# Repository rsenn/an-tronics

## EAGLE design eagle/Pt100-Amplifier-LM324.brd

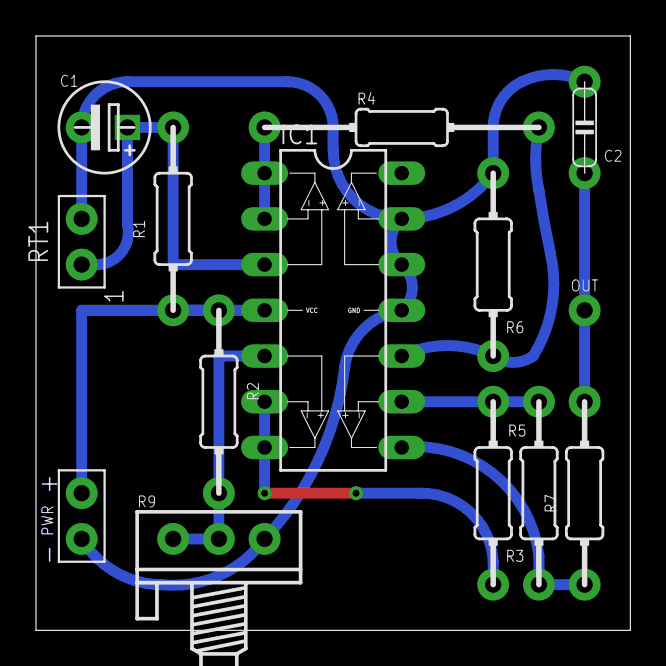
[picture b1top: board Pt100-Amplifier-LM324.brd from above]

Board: 2 copper layers, 33.0 x 33.0 mm, 14 parts (0 on the bottom side), 10 nets.

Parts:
C1: 100uF; E2,5-5
C2: 100nF; C050-020X044/V
IC1: LM324-LM324; DIL14-LM324
OUT: HPORT; SPAD
R1: 1k; 0204/10
R2: 47k; 0204/10
R3: 10k; 0204/10-V
R4: 10k; 0204/15
R5, R6: 47k; 0204/10-V
R7: 220k; 0204/10
R9: POT
RT1: SPAD-2
S5: VCC_GNDPWR-L; PWR-L

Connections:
GND: C1.-, C2.2, IC1.11, IC1.12, IC1.13, R6.2, R9.E, RT1.2, S5.1
unnamed: C1.+, IC1.3, R1.2, RT1.1
unnamed: IC1.1, IC1.2, R4.1
unnamed: IC1.10, R4.2, R6.1
unnamed: IC1.9, R3.2, R5.1
unnamed: IC1.8, R5.2, R7.1
unnamed: C2.1, OUT.1, R7.2
unnamed: IC1.6, IC1.7, R3.1
unnamed: IC1.5, R2.2, R9.A, R9.S
VCC: IC1.4, R1.1, R2.1, S5.2

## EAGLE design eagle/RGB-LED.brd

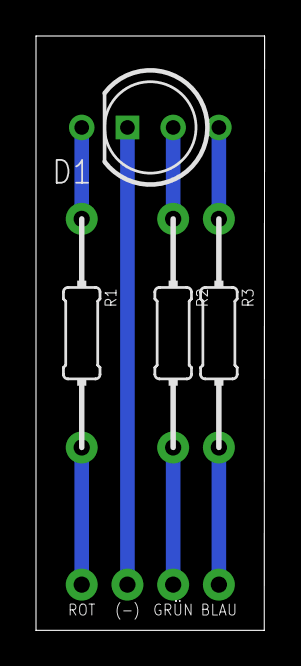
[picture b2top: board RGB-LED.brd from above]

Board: 2 copper layers, 12.7 x 33.0 mm, 8 parts (0 on the bottom side), 7 nets.

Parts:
(-): HPORT; SPAD
BLAU: HPORT; SPAD
D1: RGB-LED-5MM; LED5MM
GRÜN: HPORT; SPAD
R1: 75Ω; 0204/12-V
R2: 39Ω; 0204/12-V
R3: 27Ω; 0204/12-V
ROT: HPORT; SPAD

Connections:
unnamed: D1.1, R1.2
unnamed: D1.3, R2.2
unnamed: D1.4, R3.2
unnamed: R1.1, ROT.1
unnamed: GRÜN.1, R2.1
unnamed: BLAU.1, R3.1
unnamed: (-).1, D1.2

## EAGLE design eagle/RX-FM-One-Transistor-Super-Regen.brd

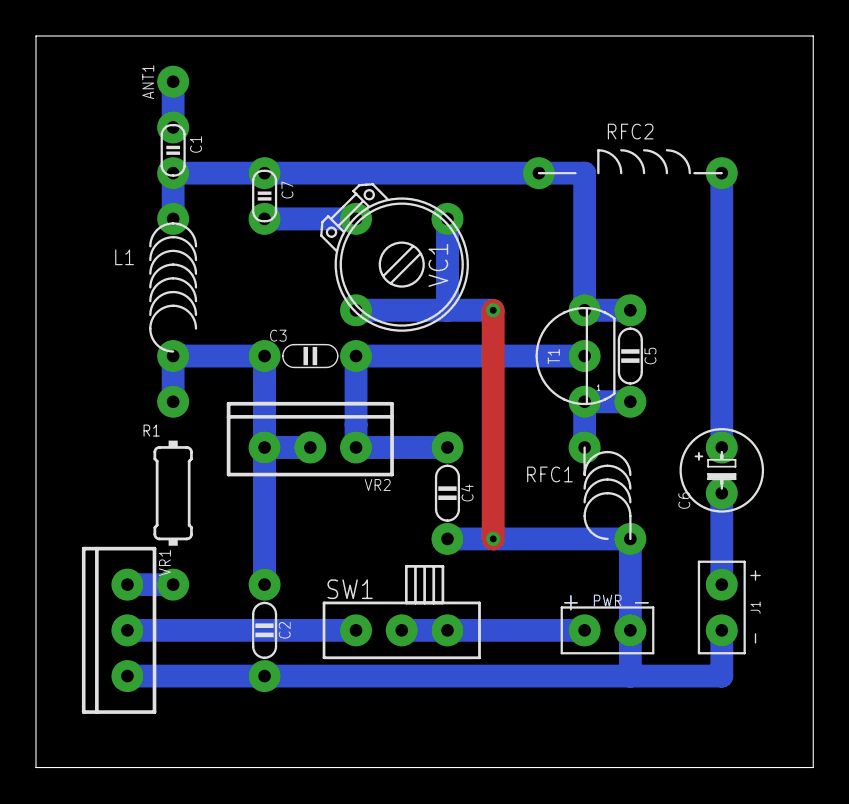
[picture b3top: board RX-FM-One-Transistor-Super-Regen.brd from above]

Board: 2 copper layers, 43.2 x 40.6 mm, 19 parts (0 on the bottom side), 12 nets.

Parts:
ANT1: ANT; SPAD
C1: 5pF; C025-015X024
C2: 0.001; C050-020X036/V
C3: 0.001; C050-020X036
C4: 100pF; C050-020X036/V
C5: 10pF; C050-020X036/V
C6: 10µF; E2,5-4
C7: 47pF; C025-015X024
J1: SPAD+-+-; SPAD+-
L1: 4t; L-04/7-V
R1: 2.2kΩ; 0204/10-V
RFC1: 10µH; L-04-2/5V
RFC2: 10µH; L-03/10
S6: VCC_GNDPWR-R; PWR-R
SW1: SW-SPST-SL-1P2T-H; SLSW-1P2T-H
T1: 2N3904; TO92
VC1: 20pF; TRIM-2222-808
VR1: 10kΩ; TRIM-POT
VR2: 100kΩ; TRIM-POT

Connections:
GND: C2.2, C4.2, J1.1, RFC1.1, S6.1, VC1.1, VC1.3, VR1.E
unnamed: ANT1.1, C1.1
unnamed: C1.2, C5.1, C7.1, L1.1, RFC2.2, T1.3
unnamed: C2.1, C3.1, L1.2, R1.1, VR2.E, VR2.S
unnamed: C7.2, VC1.2
unnamed: R1.2, VR1.A
unnamed: C5.2, RFC1.2, T1.1
unnamed: C3.2, C4.1, T1.2, VR2.A
unnamed: SW1.S, VR1.S
unnamed: C6.+, RFC2.1
unnamed: C6.-, J1.2
VCC: S6.2, SW1.P

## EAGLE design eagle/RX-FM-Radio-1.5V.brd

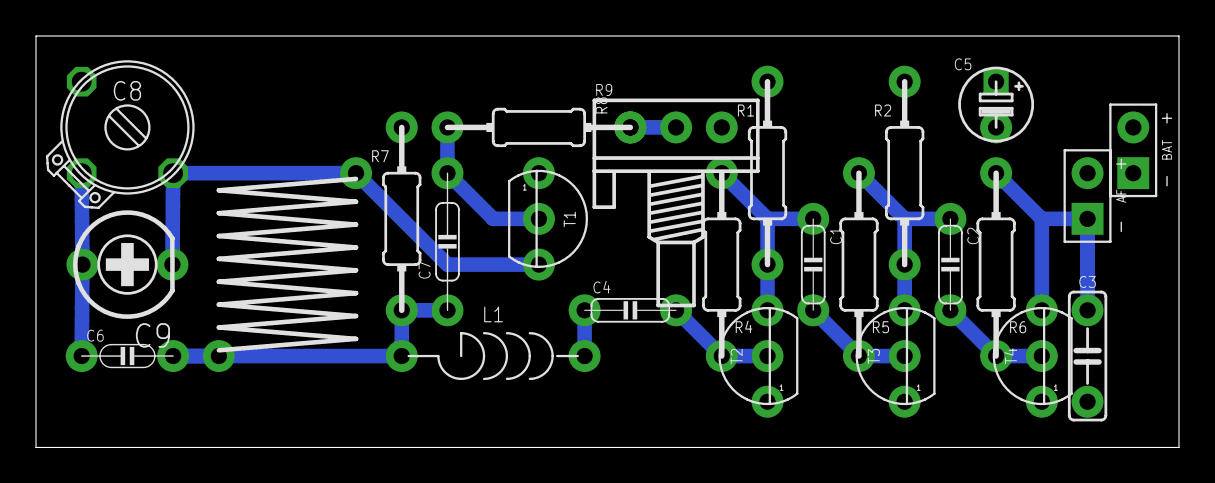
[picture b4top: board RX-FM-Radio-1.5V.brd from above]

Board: 2 copper layers, 63.5 x 22.9 mm, 25 parts (0 on the bottom side), 14 nets.

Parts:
AF: SPAD+-+-; SPAD+-
BAT: SPAD+-+-; SPAD+-
C1: 33nF; C050-020X044
C2: 100nF; C050-020X044
C3: 10nF; C050-025X060
C4: 10nF; C050-020X044
C5: 100μF; E2.5-4/V
C6: 22pF; C050-020X036
C7: 100nF; C075-020X044
C8: 20pF; TRIM-2222-808
C9: 5pF; CTRIMTZ03
L1: 2.2μH; L-03/10
L2: 0.2μH; L-10/10Y
R1, R2: 4.7kΩ; 0204/10-V
R4, R5: 1MΩ; 0204/10-V
R6: 56kΩ; 0204/10-V
R7: 10kΩ; 0204/10-V
R8: 470kΩ; 0204/10-V
R9: 10kΩ; POT
T1, T2, T3, T4: 2N2222; TO92

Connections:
BASE: C7.2, R8.2, T1.2
BIAS: R8.1, R9.S
CAP: C6.1, C8.2, C9.1
COIL: C6.2, C7.1, L1.2, L2.P$2, R7.2
COLL: C8.3, C9.2, L2.P$1, T1.3
GND: BAT.1, C3.2, C5.-, R9.E, T1.1, T2.1, T3.1, T4.1
unnamed: C1.2, R5.1, T3.2
unnamed: C2.1, R2.2, R5.2, T3.3
unnamed: C1.1, R1.2, R4.2, T2.3
unnamed: C2.2, R6.1, T4.2
unnamed: AF.1, C3.1, R6.2, T4.3
unnamed: C4.2, R4.1, T2.2
unnamed: C4.1, L1.1
VCC: AF.2, BAT.2, C5.+, R1.1, R2.1, R7.1, R9.A

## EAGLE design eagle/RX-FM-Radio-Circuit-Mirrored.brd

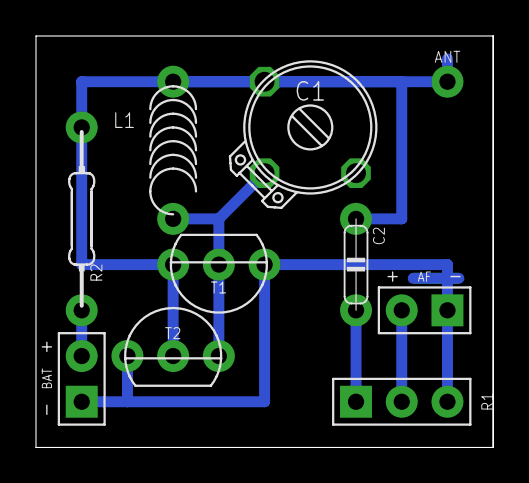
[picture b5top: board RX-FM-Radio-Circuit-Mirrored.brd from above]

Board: 2 copper layers, 25.4 x 22.9 mm, 10 parts (0 on the bottom side), 6 nets.

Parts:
AF: SPAD+-
ANT: ANT; SPAD
BAT: SPAD-+
C1: 2 - 20pF; TRIM-2222-808
C2: 220nF; C050-020X044
L1: 200nH; L-04/7-V
R1: 10kΩ; CONN-3P
R2: 10kΩ; 0204/10
T1, T2: 2N2222; TO92-EBC

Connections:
GND: AF.1, BAT.1, R1.3, T1.E, T2.E
unnamed: C1.2, L1.2, T1.B, T2.C
unnamed: C2.2, R1.1
unnamed: ANT.1, C1.1, C2.1, L1.1, R2.1, T1.C, T2.B
unnamed: AF.2, R1.2
VCC: BAT.2, R2.2

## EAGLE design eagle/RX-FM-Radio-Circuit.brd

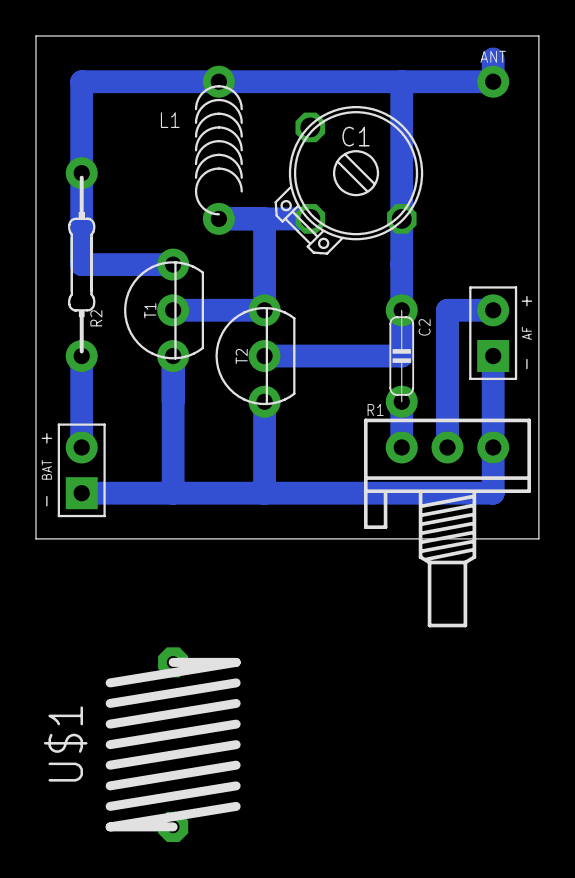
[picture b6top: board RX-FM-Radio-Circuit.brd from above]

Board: 2 copper layers, 27.9 x 27.9 mm, 11 parts (0 on the bottom side), 6 nets.

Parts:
AF: SPAD+-
ANT: ANT; SPAD
BAT: SPAD-+
C1: 2 - 20pF; TRIM-2222-808
C2: 220nF; C050-020X044
L1: 200nH; L-04/7-V
R1: 10kΩ; POT
R2: 10kΩ; 0204/10
T1, T2: 2N2222; TO92-EBC
U$1: TEST

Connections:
GND: AF.1, BAT.1, R1.E, T1.E, T2.E
unnamed: C1.2, L1.2, T1.B, T2.C
unnamed: C2.2, R1.A
unnamed: ANT.1, C1.3, C2.1, L1.1, R2.1, T1.C, T2.B
unnamed: AF.2, R1.S
VCC: BAT.2, R2.2

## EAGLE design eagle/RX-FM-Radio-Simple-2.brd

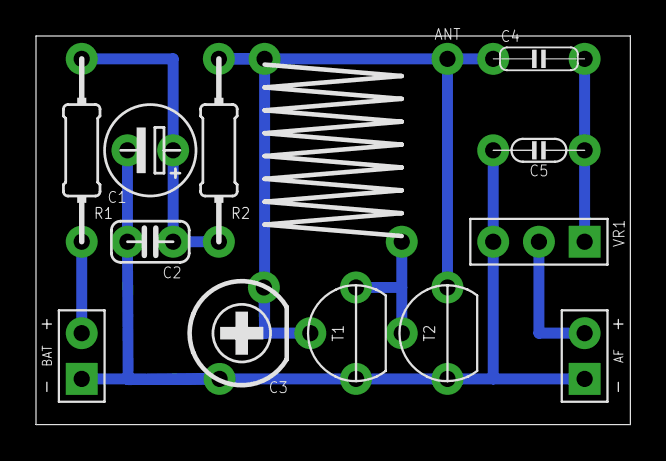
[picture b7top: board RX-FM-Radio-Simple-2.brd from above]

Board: 2 copper layers, 33.0 x 21.6 mm, 14 parts (0 on the bottom side), 7 nets.

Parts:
AF: SPAD+-+-; SPAD+-
ANT: ANT; SPAD
BAT: VCC_GNDL; SPAD-+
C1: 100µF; E2,5-5/V
C2: 100nF; C025-024X044
C3: 2 - 20pF; CTRIMBB
C4: 220nF; C050-020X044
C5: 2.2nF; C050-020X036/V
L1: 200nH; L-10/10X
R1: 1kΩ; 0204/10-V
R2: 10kΩ; 0204/10-V
T1, T2: 2N2222-A; TO92-A
VR1: 10kΩ; CONN-3P

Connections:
GND: AF.1, BAT.1, C1.-, C2.2, C3.1, C5.2, T1.1, T2.1, VR1.3
unnamed: ANT.1, C3.2, C4.1, L1.1, R2.2, T1.2, T2.3
unnamed: C1.+, C2.1, R1.2, R2.1
unnamed: C4.2, C5.1, VR1.1
unnamed: L1.2, T1.3, T2.2
unnamed: AF.2, VR1.2
VCC: BAT.2, R1.1

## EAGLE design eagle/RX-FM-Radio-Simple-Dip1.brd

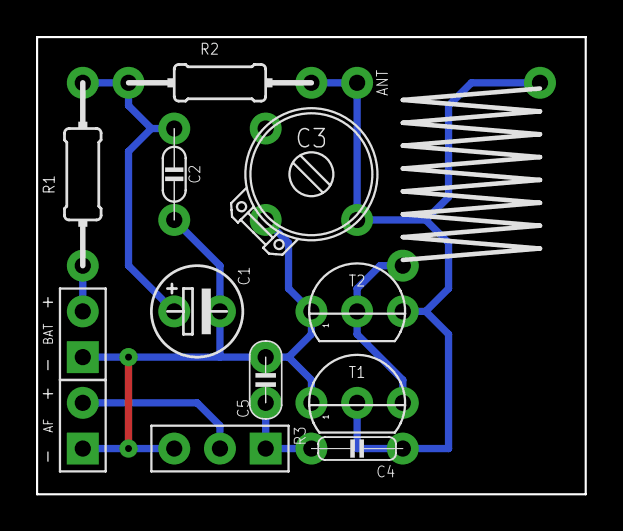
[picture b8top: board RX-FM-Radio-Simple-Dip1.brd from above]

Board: 2 copper layers, 30.5 x 25.4 mm, 14 parts (0 on the bottom side), 7 nets.

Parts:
AF: SPAD+--+; SPAD-+
ANT: ANT; SPAD
BAT: VCC_GNDL; SPAD-+
C1: 100µF; E2,5-5/V
C2: 100nF; C050-020X036/V
C3: 2 - 20pF; TRIM-2222-808
C4: 220nF; C050-020X044
C5: 2.2nF; C025-020X036
L1: 0.2µH; L-10/10Y
R1: 1kΩ; 0204/10
R2: 10kΩ; 0204/10
R3: 10kΩ; CONN-3P
T1, T2: 2N2222; TO92

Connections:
GND: AF.1, BAT.1, C1.-, C2.2, C3.2, C5.2, R3.3, T1.1, T2.1
unnamed: ANT.1, C3.3, C4.1, L1.P$1, R2.2, T1.2, T2.3
unnamed: C1.+, C2.1, R1.2, R2.1
unnamed: C4.2, C5.1, R3.1
unnamed: L1.P$2, T1.3, T2.2
unnamed: AF.2, R3.2
VCC: BAT.2, R1.1
